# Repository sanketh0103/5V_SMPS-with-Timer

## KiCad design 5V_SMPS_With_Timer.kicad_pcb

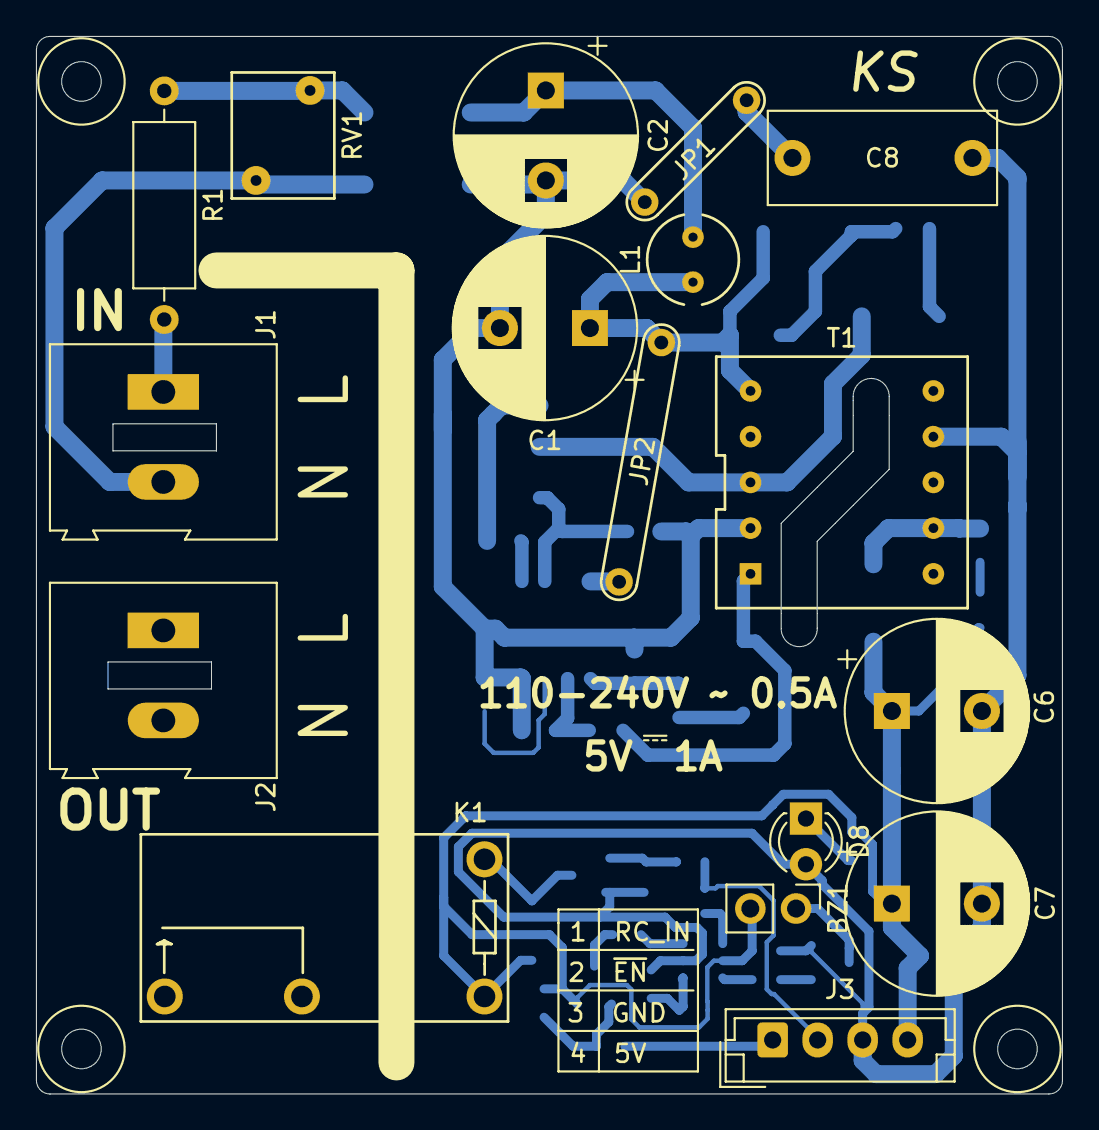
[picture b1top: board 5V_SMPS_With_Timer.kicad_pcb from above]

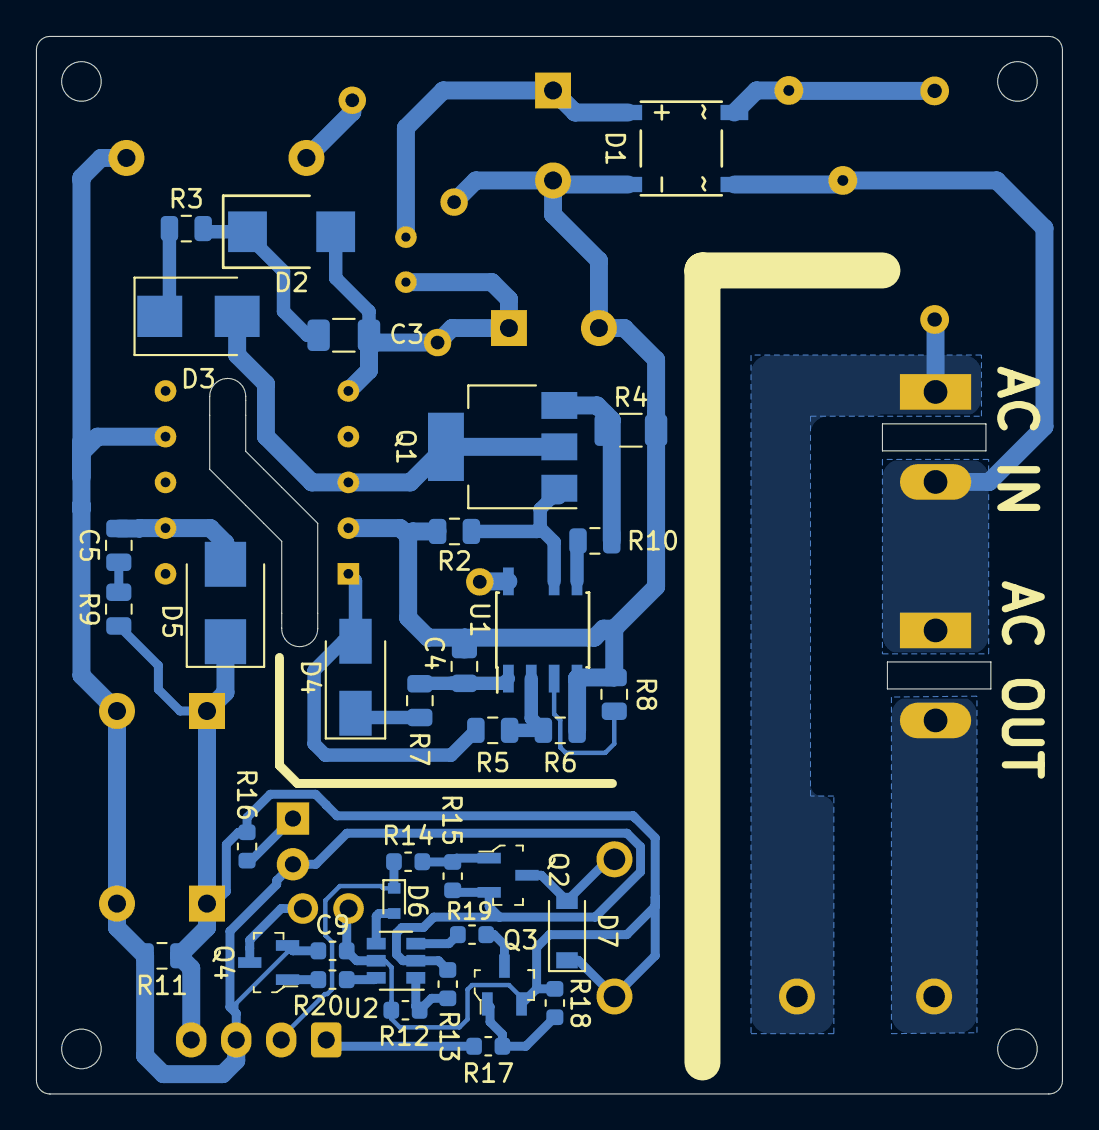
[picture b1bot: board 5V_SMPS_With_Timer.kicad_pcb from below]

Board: 2 copper layers, 57.0 x 58.8 mm, 53 parts (36 on the bottom side), 37 nets.

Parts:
BZ1: Buzzer; PinHeader_1x02_P2.54mm_Vertical
C1, C2: 4.7uF; CP_Radial_D10.0mm_P5.00mm
C3: 1nF 200V; C_1206_3216Metric
C4: 4.7uF 25V; C_0805_2012Metric
C5: 1nF 50V; C_0805_2012Metric
C6, C7: 680uF; CP_Radial_D10.0mm_P5.00mm
C8: 2.2nF X1 Y1; C_Disc_D12.5mm_W5.0mm_P10.00mm
C9: 0.1uF; C_0603_1608Metric
D1: MDB6S; MDB8S
D2: SMBJP6KE82A; D_DO-214AA_(SMB_J-Bend)
D3: MURS160-13-F; D_SMB
D4: RS1B-13-F; D_SMA
D5: B340LB-13-F; D_SMB
D6: RB520S30T5G; D_SOD-523
D7: 1N4148; D_SOD-123
D8: RED; LED_D3.0mm
J1: AC IN; TerminalBlock_Altech_AK300-2_P5.00mm
J2: AC OUT; TerminalBlock_Altech_AK300-2_P5.00mm
J3: Conn_01x04; JST_EH_B4B-EH-A_1x04_P2.50mm_Vertical
JP1: Jumper; Jumper_THT_P5mm
JP2: Jumper; Jumper_THT_P14mm
K1: 10A Relay; Relay-Panasonic-ALQ-Form-1A
L1: RLB0608-471KL 470uH; L_Radial_D5.5mm_P2.5mm
Q1: STN2580; SOT-223
Q2: 2N7002; SOT-23-3
Q3: BSS84; SOT-23-3
Q4: Q_NPN_BEC; SOT-23-3
R1: 10 1W; R_Axial_DIN0309_L9.0mm_D3.2mm_P12.70mm_Horizontal
R2, R11: 10K; R_0805_2012Metric
R3: 1.62K; R_0805_2012Metric
R4: 2.15; R_1206_3216Metric
R5: 82.5K; R_0805_2012Metric
R6: 27.4K; R_0805_2012Metric
R7: 22.5; R_0805_2012Metric
R8: N.C; R_0805_2012Metric
R9: 39; R_0805_2012Metric
R10: 1K; R_0805_2012Metric
R12, R13, R15, R18: 10K; R_0603_1608Metric
R14, R16, R17, R19, R20: 1K; R_0603_1608Metric
RV1: V250LS4P; RV_Disc_D7mm_W5.7mm_P5mm
T1: 7508110151
U1: UCC28720; SOIC-8-N7_3.9x4.9mm_P1.27mm
U2: ATtiny10-TS; SOT-23-6

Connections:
+5V: BZ1.2, C6.1, C7.1, C9.2, D5.1, D7.1, J3.4, K1.6, Q3.2, R9.1, R11.1, R12.2, R16.1, R18.1, U2.5
Earth: C1.2, C2.2, C4.2, D1.2, JP1.1, R2.2, R4.2, R6.2, R8.2, T1.2, U1.4
GND: C6.2, C7.2, C8.1, C9.1, D8.2, J3.3, Q2.2, Q4.2, R11.2, R13.1, R15.2, T1.7, U2.2
L: J1.1, K1.14, R1.2
N: D1.3, J1.2, J2.1, RV1.1
unnamed: BZ1.1, Q4.3
unnamed: C1.1, C3.2, D2.2, JP2.2, L1.2, T1.5
unnamed: C2.1, D1.1, L1.1
unnamed: C3.1, D2.1, R3.2
unnamed: C4.1, R7.2, U1.1
unnamed: C5.1, R9.2
unnamed: C5.2, D5.2, T1.9
unnamed: C8.2, JP1.2
unnamed: D1.4, R1.1, RV1.2
unnamed: D3.1, R3.1
unnamed: D3.2, Q1.2, T1.3
unnamed: D4.1, R7.1
unnamed: D4.2, R5.1, T1.1
unnamed: D6.2, U2.4
unnamed: D7.2, K1.2, Q2.3
unnamed: D8.1, R16.2
unnamed: JP2.1, U1.8
unnamed: Q1.1, R2.1, U1.6
unnamed: Q1.3, R4.1, R10.2
unnamed: Q2.1, R14.1, R15.1
unnamed: Q3.1, R17.1, R18.2
unnamed: Q3.3, R19.1
unnamed: Q4.1, R20.2
unnamed: R5.2, R6.1, U1.2
unnamed: R8.1, U1.3
unnamed: R10.1, U1.5
unnamed: R19.2, U2.3
unnamed: R20.1, U2.6
OUT: J2.2, K1.8
RC_IN: D6.1, J3.2, R14.2
T_SEL: R12.1, R13.2, U2.1
~EN: J3.1, R17.2
